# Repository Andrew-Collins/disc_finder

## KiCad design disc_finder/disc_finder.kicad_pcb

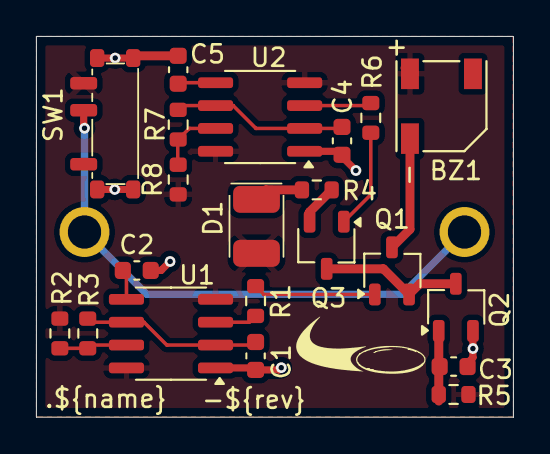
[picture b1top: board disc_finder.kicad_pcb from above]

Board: 2 copper layers, 26.5 x 21.1 mm, 22 parts (1 on the bottom side), 18 nets.

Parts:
BZ1: Buzzer; CUI_CMT-5023S-SMT
C1: 0.1u; C_0603_1608Metric
C2, C5: 10n; C_0603_1608Metric
C3, C4: 10u; C_0603_1608Metric
D1: LED; LED_OSRAM_TOPLED
J1: Battery; 3003
Q1, Q2, Q3: DMN6140L-7; TSOT-23
R1, R6: 10k; R_0603_1608Metric
R2, R8: 0R; R_0603_1608Metric
R3: 1k; R_0603_1608Metric
R4: 100R; R_0603_1608Metric
R5: 10M; R_0603_1608Metric
R7: 100k; R_0603_1608Metric
SW1: CUS-12TB
U1, U2: ICM7555xB; SOIC-8_3.9x4.9mm_P1.27mm

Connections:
+BATT: J1.1, SW1.2
/BZR_TMR_OUT: Q1.1 (G), R1.1
/LED_TMR_OUT: Q3.1 (G), R6.1
/TR: C4.1, R7.1, U2.2 (TR), U2.6 (THR)
/TR_B: C1.1, R3.1, U1.2 (TR), U1.6 (THR)
GND: C1.2, C2.2, C3.2, C4.2, C5.2, J1.2, Q2.2 (S), SW1.MP, U1.1 (GND), U2.1 (GND)
unnamed: BZ1.2 (-), Q1.3 (D)
unnamed: D1.1 (K), R4.1
unnamed: Q1.2 (S), Q2.3 (D), Q3.3 (D)
unnamed: C3.1, Q2.1 (G), R5.2
unnamed: Q3.2 (S), R4.2
unnamed: C2.1, U1.5 (CV)
unnamed: R2.2, R3.2, U1.7 (DIS)
unnamed: R1.2, U1.3 (Q)
unnamed: C5.1, U2.5 (CV)
unnamed: R7.2, R8.2, U2.7 (DIS)
unnamed: R6.2, U2.3 (Q)
VDD: BZ1.1 (+), D1.2 (A), R2.1, R5.1, R8.1, SW1.3, U1.4 (R), U1.8 (VCC), U2.4 (R), U2.8 (VCC)

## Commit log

2024-08-04 Completed sch and pcb. Implementing CI
2024-08-04 Switched over to github
2024-08-04 Remove commands stuff from ci
2024-08-04 Added PCB CI stuff and for main too
2024-08-04 Increased 555 timer frequency so that buzzer is audible, and delayed initial operation using RC
2024-08-04 Fixup CI trigger on kicad files
2024-08-04 Now using a bright orange LED, and moved it to the middle of the board
2024-08-06 Added an additional 555 timer for the led
2024-08-06 Dummy commit to run CI on main
2024-08-06 Updated CI to run on kibot settings edit
2024-08-06 Added a logo, name and revision to PCB
2024-08-06 Moved name over on PCB
2024-08-06 Fixed up name var to remove kicad suffix
2024-08-06 Attempting to use tagpr to automate releases
2024-08-07 Attempting to tag and release properly
2024-08-07 Added git setup step to main action
2024-08-07 Permissions setup properly, and using external job template to push
2024-08-07 Zip not on debian by default
2024-08-07 Set tag name explicitly in release step
2024-08-07 Add -r flag to zip command to actually zip up all the files.
2024-08-07 Attempt to capture zip files in fab folder recursively
2024-08-07 Trying to fixup kibot rev
2024-08-07 Update kicad page vars with vars that are filled by kibot
2024-08-07 Limit length of commit hash in rev for dev branch
2024-08-07 Put the version into the jlc zip output
2024-09-12 Added battery holder step file and corrected LED nmos orientation
2024-09-12 Added freecad file of holder
